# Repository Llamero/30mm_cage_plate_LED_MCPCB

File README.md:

# 30 mm Cage Plate LED Driver

## 4x LED 30 mm Cage Plate Board Description:
This board is an entirely self-contained LED and driver circuitry designed to be compatible with the Thorlabs 30 mm cage plate system: https://www.thorlabs.com/navigation.cfm?guide_id=2004  

The LEDs on the board are closely spaced so that all four LEDs efficiently couple into a 5 mm liquid light guide or other optical paths.

Each board can drive up to four individual LEDs, and includes a thermistor for temperature monitoring.  The the LED current is regulated by an [AL8843](https://www.diodes.com/part/view/AL8843), allowing LEDs to be driven with up to three amps of current.  The [AL8843](https://www.diodes.com/part/view/AL8843) also allows for both PWM control as well as analog current control down to 10% of the current limit (see below for setting max current limit).

Four p-channel mosfets on the board create a 1x4 multiplexer that allows individual LEDs to be toggled on by pulling the corresponding LED channel's gate to ground.  Each gate has a 4.7 kOhm pullup resistor so that each channel defaults to being off if not connected.

To turn the LEDs off more rapidly, there is also a 38V TVS diode parallel to the inductor that can be used to dump the residual energy stored in the inductor by setting all four multiplexer channels high.

A heatsink and fan can also be mounted to the backside of the cage plate for active cooling of high-current LEDs.

## 3x 30 mm Cage Plate Controller Description:
This repository also includes the design files for a controller that can operate up to three 30 mm cage plates for a total of 12 LEDs.

The controller is powered by a Teensy 4.1 which allows for precise timing control (<10 ns hysteresis) of each LED, as well a complex programmable control.  

On the back of the driver, each board connects to the driver via a shielded cat5 ethernet cable.  Additionally, there is a cat5 port with both a 12V supply and three channels of 5V PWM outputs for both powering the fans for each board as well as controlling the fan speed.  Finally, there are four protected digital inputs allowing for control signals up to -15V/+18V.

On the front of the driver, there is a potentiometer for controlling the intensity of each of the three LED boards, as well as a pushbutton to select the channel for each board.  Additionally, each pushbutton includes a red-green LED indicator to indicate which of the four LED channels is active.

## Driver Software:
There is software prewritten for the Teensy 4.1 that allows for both manual and programmable control, for syncing to triggers or other inputs.

Additionally, there is a GUI that allows for software control of the LED driver, we well as access to five preset programmable sync modes (digital, analog, confocal, serial, and custom), as well as custom configuration of the LED driver.

## Design:
To view and modify the board, download KiCAD https://www.kicad.org/, and open the project file.

Make sure to modify the LED footprint to match the footprint for your desired LEDs, and to change the current limit resistor to the desired value (see [AL8843](https://www.diodes.com/part/view/AL8843) datasheet, p. 11):
```
RSET (Ω)  Nominal Average Output Current (mA)
0.033     3,000
0.05      2,000
0.067     1,500
0.1       1,000
0.15      667
0.3       333
```
When changing the LED footprints, ensure that the LEDs remain closely spaced for efficient coupling into a liquid light guide.

## Ordering:
The BOM can be found here: 

This BOM includes all the parts needed to build both the LED driver boards as well as the LED controller board.

To order the PCBs, upload the Gerber files to your desired PCB vendor, such as: [https://www.pcbway.com/project/shareproject/W55957ASK98_30_mm_Cage_Plate_LED_MCPCB_kicad_pcb_3d2c1975.html](https://www.pcbway.com/project/shareproject/W55957ASK98_30_mm_Cage_Plate_LED_MCPCB_kicad_pcb_3d2c1975.html)  Make sure that the LED boards are MCPCBs and not FR4.  The driver board can be ordered as an FR4 board.

## Assembly:
To start, spread [thermal epoxy](https://www.digikey.com/en/products/detail/mg-chemicals/8329TCM-6ML/6035511) onto the flat side of a [Thorlabs 30 mm blank cage plate](https://www.thorlabs.com/thorproduct.cfm?partnumber=CP31).

Press the MCPCB board firmly to the cage plate using a vise or heavy weights.

Use a pipette tip or other fine tipped tool to remove excess epoxy from the cage rod holes.

Slide the board across the cage plate as needed to align the cage rod holes and allow the epoxy to cure overnight.

Next, assemble the board similarly to other reflow soldering boards. See the following manual: https://github.com/Llamero/Light_Color_and_Intensity_Datalogger/blob/master/Data%20logger%20assembly%20manual.pdf

Finally, use thermal epoxy to connect the heatsink to the Thorlabs cage plate, press firmly, and bake at 50°C overnight to cure.

.jpg)

## Operation:
Connect a 5V to 20V power supply, with the positive terminal connected to the Vin pin and the negative terminal connected to the Gnd pin. To control the LED current, you can send a +0.4V (10% current) to +2.5V (100% current) to the Ctrl pin. The LED can also be dimmed with PWM with a voltage up to 5V.  To control the mux, pull the channel you want to turn on to ground (0V).  To monitor temperature, measure the resistance of the thermistor.

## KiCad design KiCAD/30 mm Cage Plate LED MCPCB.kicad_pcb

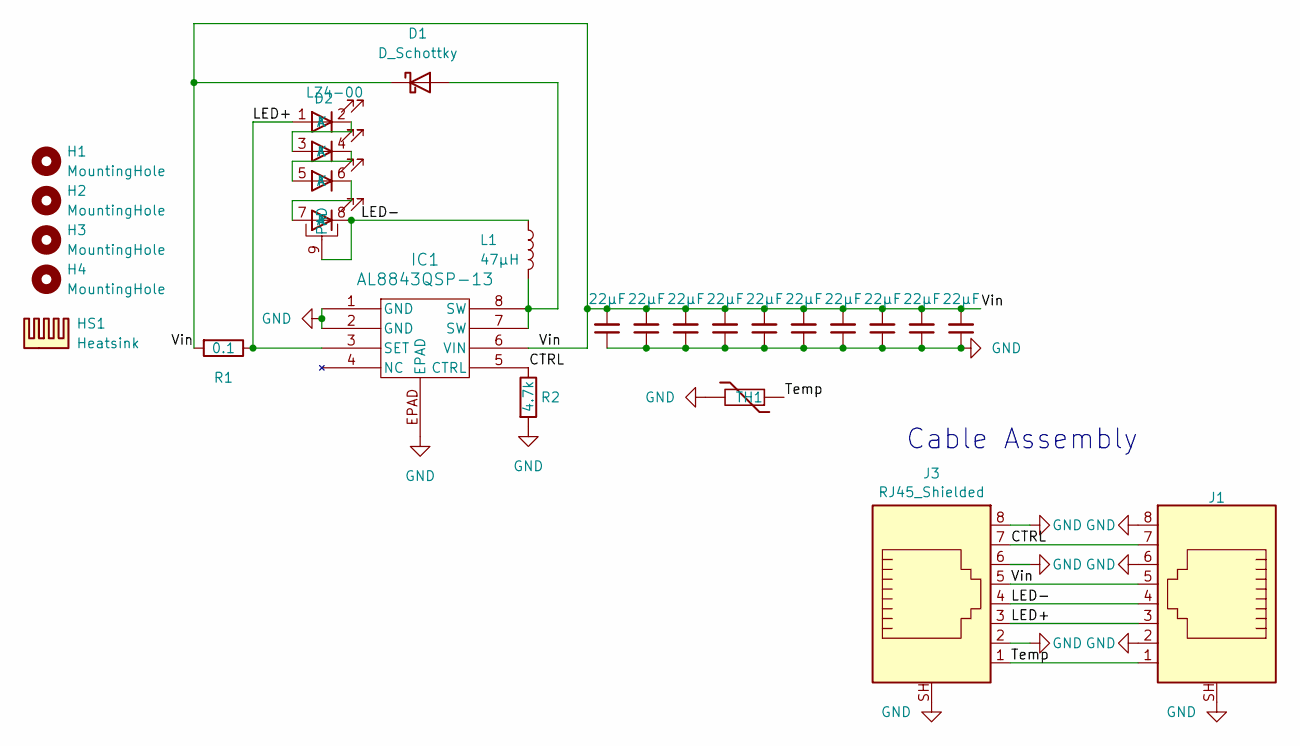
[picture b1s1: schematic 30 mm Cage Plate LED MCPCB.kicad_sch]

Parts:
C1, C2, C3, C4, C5, C6, C7, C8, C9, C10: 22µF; C_0805_2012Metric; Part CL21A226MAYNNNE
D1: D_Schottky; D_SOD-128; Part PMEG10030ELPX
D2: LZ4-00; Part LZ4-00R308-0000
H1, H2, H3, H4: MountingHole; 6MM NPTH
HS1: Heatsink; Part HSB38-707025P
IC1: AL8843QSP-13; SO-8EP_3P9X4P95_DIO; Part AL8843QSP-13
J1: 8P8C_Shielded; 1x RJ45; Part RJE3A1886102N
J3: RJ45_Shielded; Part AMJF0808-0100-GNB-26
L1: 47μH; SRP1038A-220M_BRN; Part SRP1038A-470M
R1: 0.1; R_1206_3216Metric; Part D1WRL1206L4R100D-T5
R2: 4.7k; C_0603_1608Metric; Part RG1608P-472-B-T5
TH1: Thermistor; R_0603_1608Metric; Part NCP18XM472J03RB

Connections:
/CTRL: IC1.5 (CTRL), J1.7, J3.7, R2.1
/LED+: D2.1 (A), IC1.3 (SET), J1.3, J3.3, R1.1
/LED-: D2.8 (K), D2.9 (PAD), J1.4, J3.4, L1.1
/Temp: J1.1, J3.1, TH1.1
/Vin: C1.2, C2.2, C3.2, C4.2, C5.2, C6.2, C7.2, C8.2, C9.2, C10.2, D1.1 (K), IC1.6 (VIN), J1.5, J3.5, R1.2
GND: C1.1, C2.1, C3.1, C4.1, C5.1, C6.1, C7.1, C8.1, C9.1, C10.1, IC1.1 (GND), IC1.2 (GND), IC1.EPAD, J1.2, J1.6, J1.8, J1.SH, J3.2, J3.6, J3.8, J3.SH, R2.2, TH1.2
unnamed: D1.2 (A), IC1.7 (SW), IC1.8 (SW), L1.2
unnamed: D2.2 (K), D2.3 (A)
unnamed: D2.4 (K), D2.5 (A)
unnamed: D2.6 (K), D2.7 (A)

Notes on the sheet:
Cable Assembly

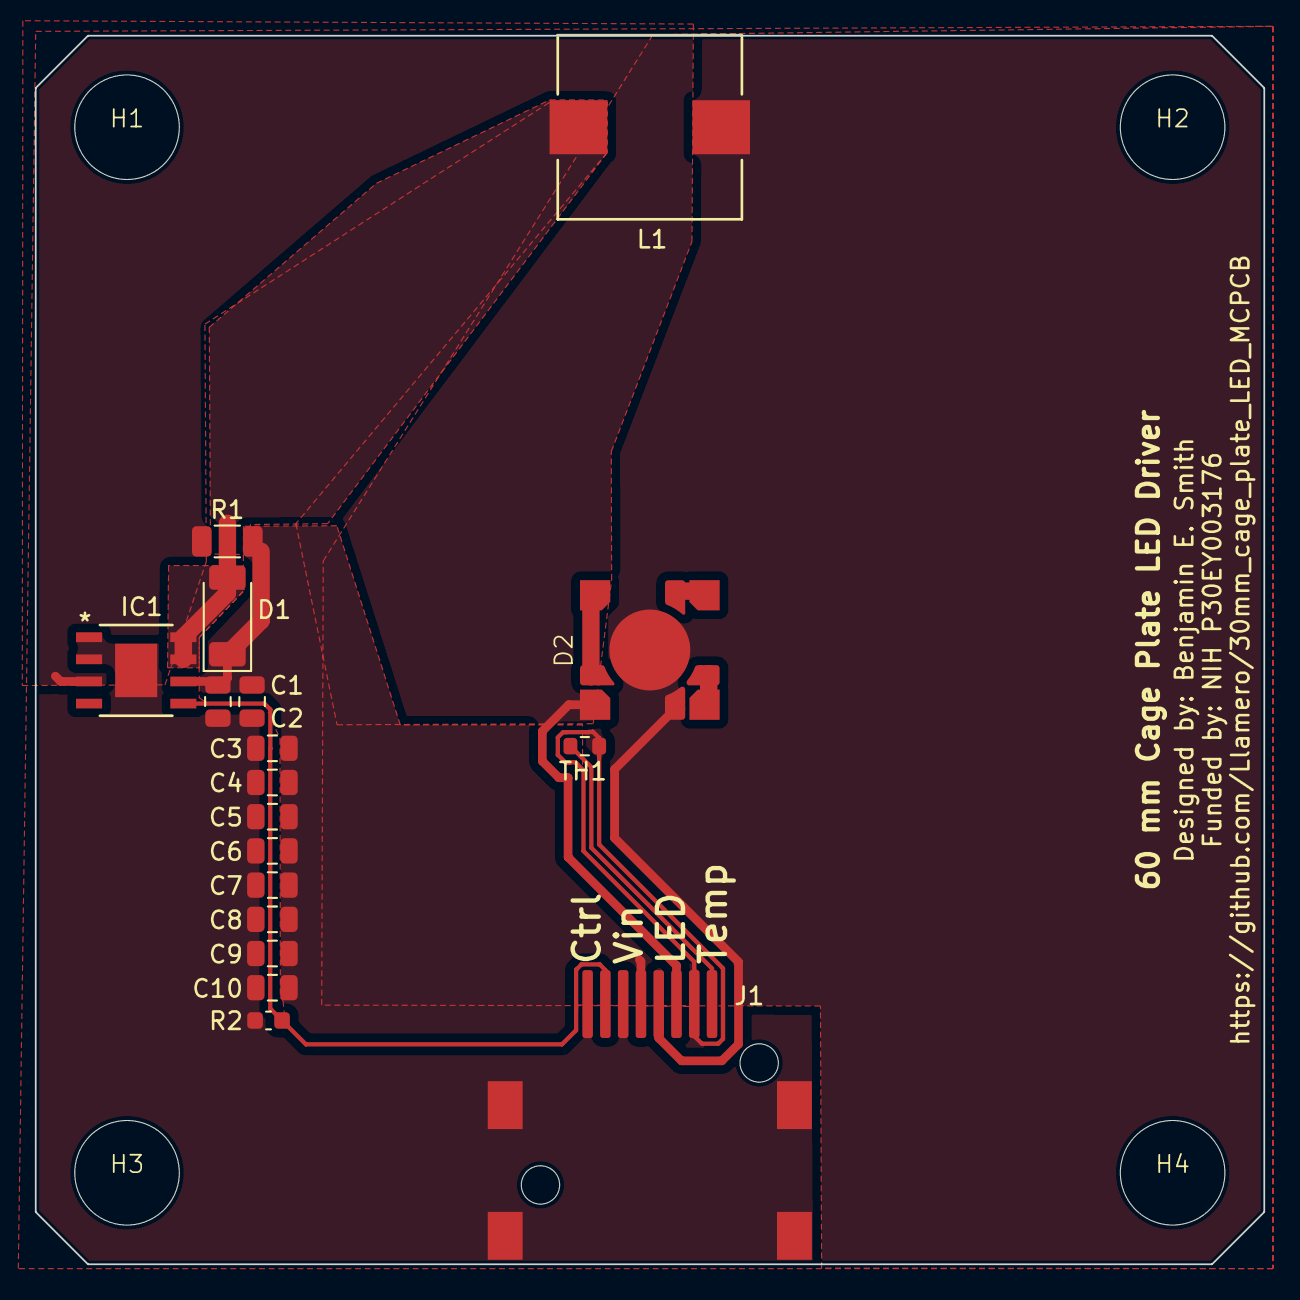
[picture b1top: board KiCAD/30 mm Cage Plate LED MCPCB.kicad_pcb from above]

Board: 2 copper layers, 70.5 x 70.5 mm, 22 parts (0 on the bottom side), 10 nets.

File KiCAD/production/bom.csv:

Designator,Footprint,Quantity,Value,LCSC Part #
"C1, C10, C2, C3, C4, C5, C6, C7, C8, C9",0805,10,22µF,
D1,D_SOD-128,1,D_Schottky,
D2,LZ4-00,1,LZ4-00,
"H1, H2, H3, H4",6MM NPTH,4,MountingHole,
IC1,SO-8EP_3P9X4P95_DIO,1,AL8843QSP-13,
J1,1x RJ45,1,8P8C_Shielded,
L1,SRP1038A-220M_BRN,1,47μH,
R1,1206,1,0.1,
R2,0603,1,4.7k,
TH1,0603,1,Thermistor,

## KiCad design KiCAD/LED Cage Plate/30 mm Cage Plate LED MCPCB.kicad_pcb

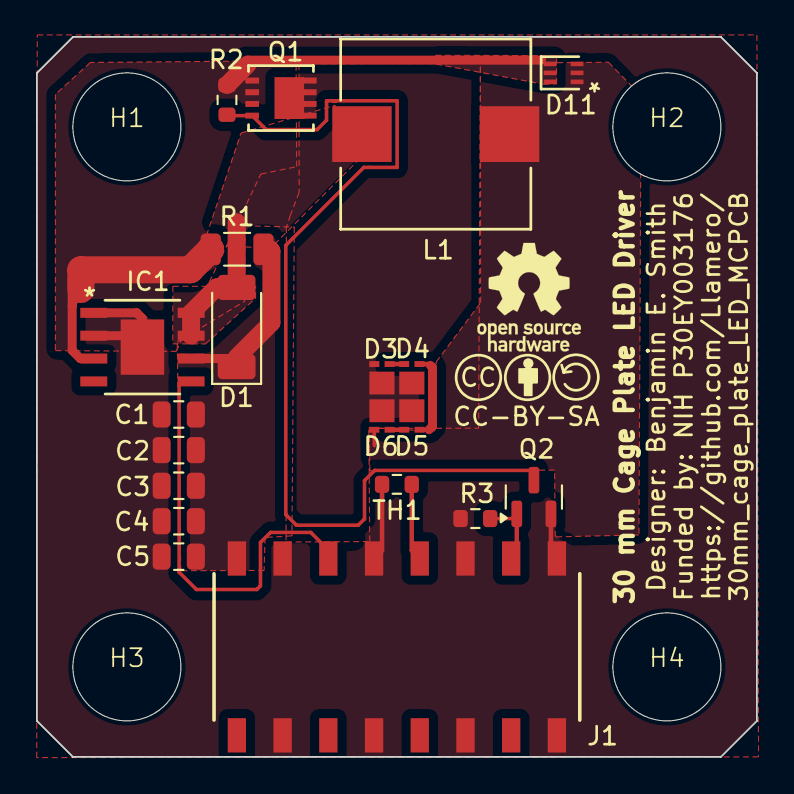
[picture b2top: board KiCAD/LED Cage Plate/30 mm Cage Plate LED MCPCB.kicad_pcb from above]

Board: 2 copper layers, 40.0 x 40.0 mm, 26 parts (0 on the bottom side), 13 nets.

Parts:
C1, C2, C3, C4, C5: 22μF; C_0805_2012Metric
D1: D_Schottky; D_SOD-128
D3, D4, D5, D6: LED_Pad; LED_XLAMP_XE-G_CRW
D11: D_Zener; DFN6_TDS3011_SEM
H1, H2, H3, H4: MountingHole; 6MM NPTH
IC1: AL8843QSP-13; SO-8EP_3P9X4P95_DIO
J1: Conn_01x08_Socket; SAMTEC_SSM-108-F-SH-TR
L1: 47μH; SRP1038A-220M_BRN
Q1: Q_PMOS; SON8_DMP4025SFGQ-13_DIO
Q2: Q_NMOS; SOT-23
R1: 0.040; R_1206_3216Metric
R2, R3: 10k; R_0603_1608Metric
SYM1: Logo_Open_Hardware_Small; OSHW-Logo_5.7x6mm_SilkScreen
SYM2: Logo_Open_Hardware_Small; CC-BY-SA Symbol
TH1: Thermistor; R_0603_1608Metric

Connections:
/Gate: J1.7, Q2.1 (G), R3.1
/LED+: D11.1 (K), IC1.3 (SET), Q1.1 (S), R1.1, R2.1
/LED-: D6.1 (K), D11.2 (A), L1.1
/PWM: IC1.5 (CTRL), J1.3
/Temp: J1.5, TH1.2
/Vin: C1.2, C2.2, C3.2, C4.2, C5.2, D1.1 (K), IC1.6 (VIN), J1.1, R1.2
GND: C1.1, C2.1, C3.1, C4.1, C5.1, IC1.1 (GND), IC1.2 (GND), IC1.EPAD, J1.2, J1.4, J1.6, J1.8, Q2.2 (S), R3.2, TH1.1
unnamed: D1.2 (A), IC1.7 (SW), IC1.8 (SW), L1.2
unnamed: D3.2 (A), D3.3 (PAD), D4.3 (PAD), D5.3 (PAD), D6.3 (PAD), Q1.3 (D)
unnamed: D3.1 (K), D4.2 (A)
unnamed: D4.1 (K), D5.2 (A)
unnamed: D5.1 (K), D6.2 (A)
unnamed: Q1.2 (G), Q2.3 (D), R2.2

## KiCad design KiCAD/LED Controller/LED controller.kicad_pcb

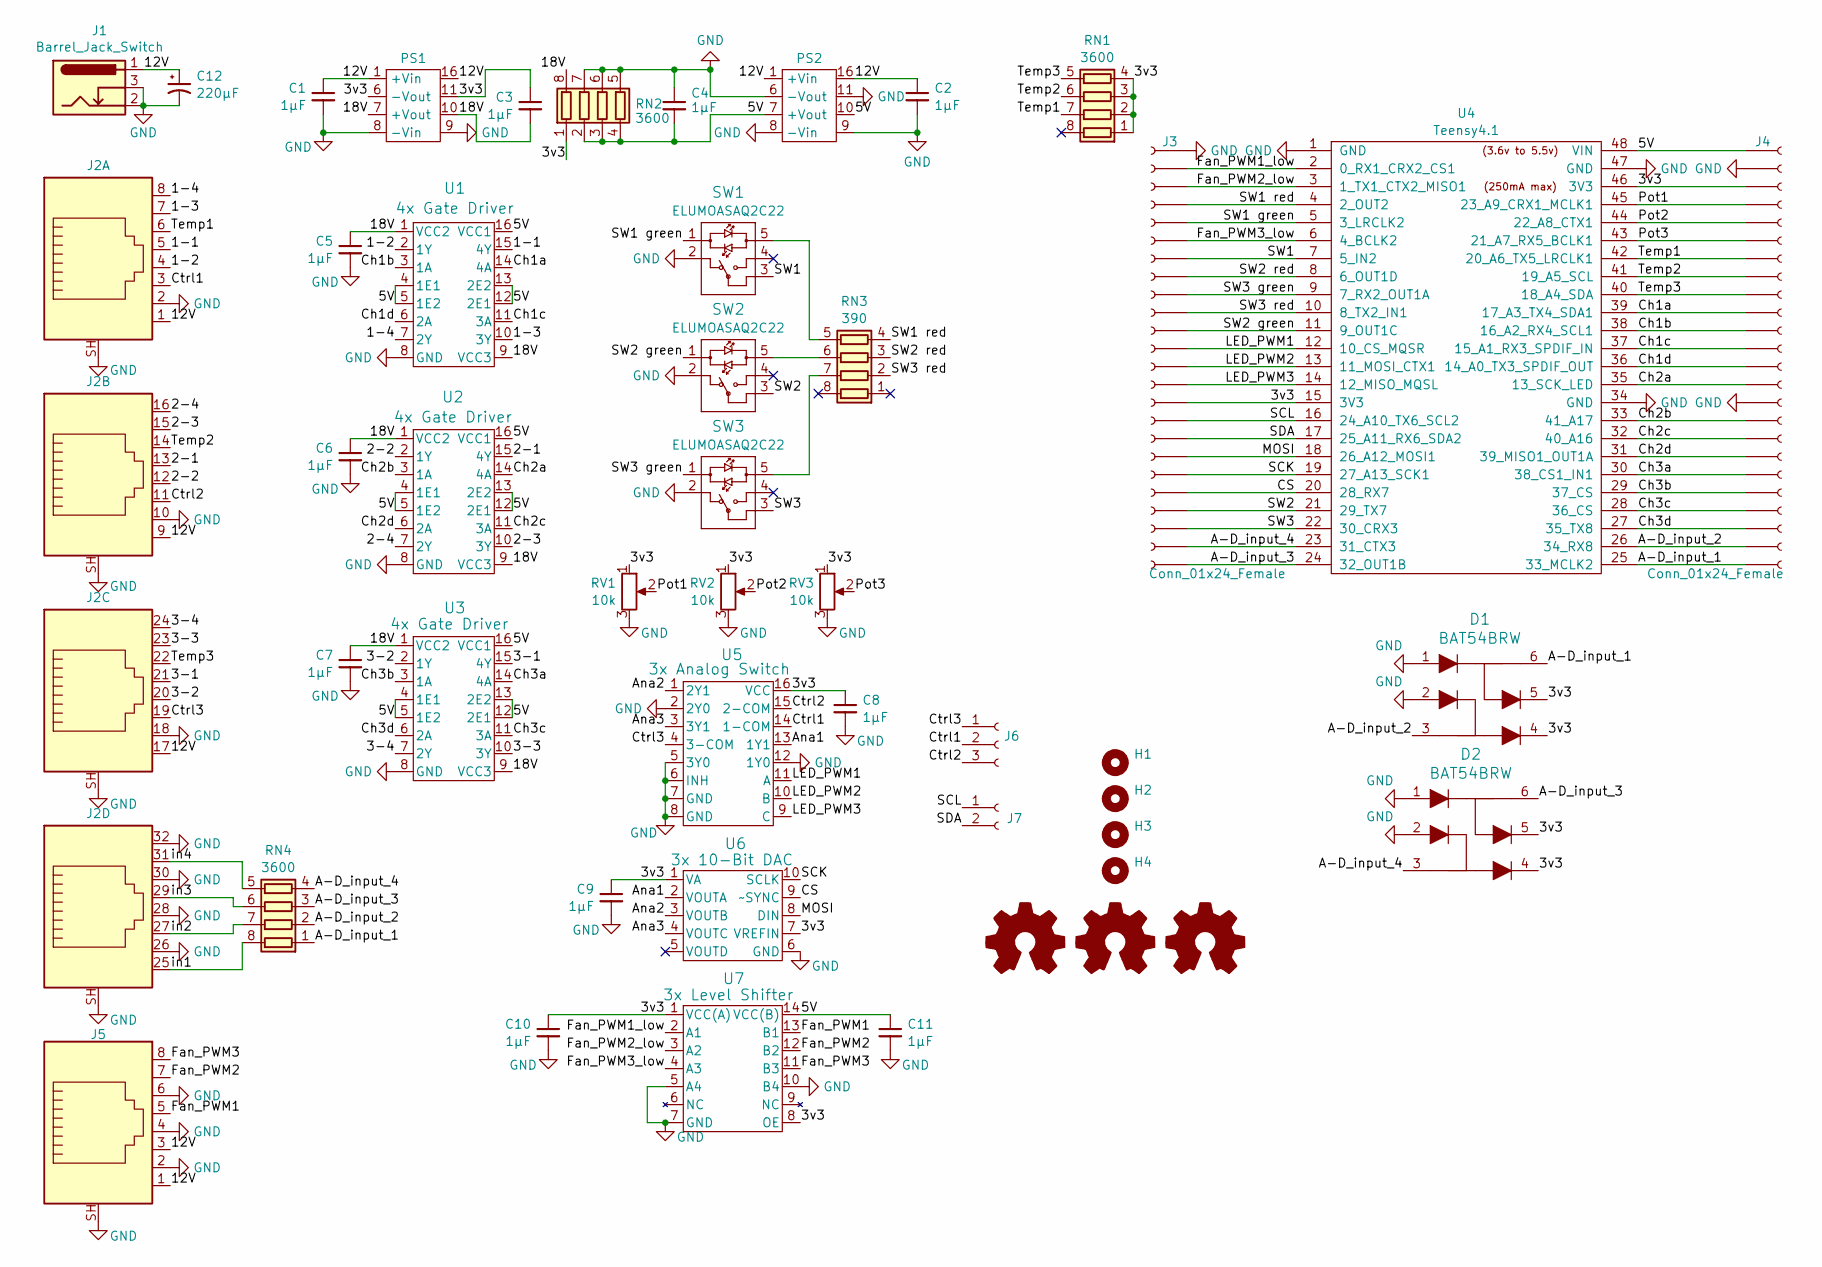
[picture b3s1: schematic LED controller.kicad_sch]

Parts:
C1, C2, C3, C4, C5, C6, C7, C8, C9, C10, C11: 1µF; C_0603_1608Metric; Part CL10A105KB8NNNC
C12: 220µF; CP_Radial_D6.3mm_P2.50mm; Part 25YXJ220M6.3X11
D1, D2: BAT54BRW; SOT-363_SC-70-6; Part BAT54BRW-7-F
H1, H2, H3, H4: MountingHole; 1-4_20 standoff; Part TN10-40-1/420-2
J1: Barrel_Jack_Switch; DC-jack_54-00165; Part # 54-00165
J2: 4x RJ45; RJ45_x4-RJSSE-5380-04; Part RJSSE-5380-04
J3, J4: Conn_01x24_Female; Part SSM-124-L-SV-LC
J5: 8P8C_Shielded; 1x RJ45; Part RJE3A1886102N
J6: Conn_01x03_Socket; PinSocket_1x03_P2.54mm_Vertical_SMD_Pin1Left; Part M20-7860346
J7: Conn_01x02_Socket; PinSocket_1x02_P2.54mm_Vertical; Part RS1-02-G
PS1: 15V DC-DC; SRS-1215-2; Part SRS-1215-2
PS2: 15V DC-DC; SRS-1215-2; Part SRS-1205-2
RN1, RN2, RN4: 3600; R_Array_Convex_4x0603; Part CAY16-362J4LF
RN3: 390; R_Array_Convex_4x0603; Part YC164-JR-07390RL
RV1, RV2, RV3: 10k; P160KN2-4QC20B10K; Part P160KN2-0QA25B10K
SW1, SW2, SW3: ELUMOASAQ2C22; ELUMOASAQ2C22_CNK; Part ELUMOASAQ2C22
SYM1: Logo_Open_Hardware_Small; CC-BY-SA Symbol
SYM2: Logo_Open_Hardware_Small; OSHW-Logo_5.7x6mm_SilkScreen
SYM3: Logo_Center_Positive; Polarity
U1, U2, U3: 4x Gate Driver; D16-4x gate driver; Part SN75374D
U4: Teensy4.1; Teensy_3_6_with_headers; Part 1568-DEV-16996-ND
U5: 3x Analog Switch; SN74LV4053ADR; Part SN74LV4053ADR
U6: 3x 10-Bit DAC; DAC084S085CIMMXNOPB; Part DAC104S085QIMMX/NOPB
U7: 3x Level Shifter; TSSOP14_NXB0104_NEX; Part NXB0104PWJ

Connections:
/1-1: J2.5, U1.15 (4Y)
/1-2: J2.4, U1.2 (1Y)
/1-3: J2.7, U1.10 (3Y)
/1-4: J2.8, U1.7 (2Y)
/2-1: J2.13, U2.15 (4Y)
/2-2: J2.12, U2.2 (1Y)
/2-3: J2.15, U2.10 (3Y)
/2-4: J2.16, U2.7 (2Y)
/3-1: J2.21, U3.15 (4Y)
/3-2: J2.20, U3.2 (1Y)
/3-3: J2.23, U3.10 (3Y)
/3-4: J2.24, U3.7 (2Y)
/3v3: C3.1, C8.1, C9.1, C10.1, D1.4, D1.5, D2.4, D2.5, J3.~, J4.~, PS1.6 (-Vout), PS1.11, RN1.1 (R1.1), RN1.2 (R2.1), RN1.3 (R3.1), RN1.4 (R4.1), RN2.1 (R1.1), RV1.1, RV2.1, RV3.1, U4.15 (3V3), U4.46 (3V3), U5.16 (VCC), U6.1 (VA), U6.7 (VREFIN), U7.1 (VCC(A)), U7.8 (OE)
/5V: C4.2, C11.1, J4.~, PS2.7 (+Vout), PS2.10, RN2.2 (R2.1), RN2.3 (R3.1), RN2.4 (R4.1), U1.4 (1E1), U1.5 (1E2), U1.12 (2E1), U1.13 (2E2), U1.16 (VCC1), U2.4 (1E1), U2.5 (1E2), U2.12 (2E1), U2.13 (2E2), U2.16 (VCC1), U3.4 (1E1), U3.5 (1E2), U3.12 (2E1), U3.13 (2E2), U3.16 (VCC1), U4.48 (VIN), U7.14 (VCC(B))
/12V: C1.1, C2.1, C12.1, J1.1, J2.1, J2.9, J2.17, J5.1, J5.3, PS1.1 (+Vin), PS1.16, PS2.1 (+Vin), PS2.16
/18V: C3.2, C5.1, C6.1, C7.1, PS1.7 (+Vout), PS1.10, RN2.8 (R1.2), U1.1 (VCC2), U1.9 (VCC3), U2.1 (VCC2), U2.9 (VCC3), U3.1 (VCC2), U3.9 (VCC3)
/A-D_input_1: D1.6, J4.~, RN4.1 (R1.1), U4.25 (33_MCLK2)
/A-D_input_2: D1.3, J4.~, RN4.2 (R2.1), U4.26 (34_RX8)
/A-D_input_3: D2.6, J3.~, RN4.3 (R3.1), U4.24 (32_OUT1B)
/A-D_input_4: D2.3, J3.~, RN4.4 (R4.1), U4.23 (31_CTX3)
/Ana1: U5.13 (1Y1), U6.2 (VOUTA)
/Ana2: U5.1 (2Y1), U6.3 (VOUTB)
/Ana3: U5.3 (3Y1), U6.4 (VOUTC)
/CS: J3.~, U4.20 (28_RX7), U6.9 (~SYNC)
/Ch1a: J4.~, U1.14 (4A), U4.39 (17_A3_TX4_SDA1)
/Ch1b: J4.~, U1.3 (1A), U4.38 (16_A2_RX4_SCL1)
/Ch1c: J4.~, U1.11 (3A), U4.37 (15_A1_RX3_SPDIF_IN)
/Ch1d: J4.~, U1.6 (2A), U4.36 (14_A0_TX3_SPDIF_OUT)
/Ch2a: J4.~, U2.14 (4A), U4.35 (13_SCK_LED)
/Ch2b: J4.~, U2.3 (1A), U4.33 (41_A17)
/Ch2c: J4.~, U2.11 (3A), U4.32 (40_A16)
/Ch2d: J4.~, U2.6 (2A), U4.31 (39_MISO1_OUT1A)
/Ch3a: J4.~, U3.14 (4A), U4.30 (38_CS1_IN1)
/Ch3b: J4.~, U3.3 (1A), U4.29 (37_CS)
/Ch3c: J4.~, U3.11 (3A), U4.28 (36_CS)
/Ch3d: J4.~, U3.6 (2A), U4.27 (35_TX8)
/Ctrl1: J2.3, J6.2, U5.14 (1-COM)
/Ctrl2: J2.11, J6.3, U5.15 (2-COM)
/Ctrl3: J2.19, J6.1, U5.4 (3-COM)
/Fan_PWM1: J5.5, U7.13 (B1)
/Fan_PWM1_low: J3.~, U4.2 (0_RX1_CRX2_CS1), U7.2 (A1)
/Fan_PWM2: J5.7, U7.12 (B2)
/Fan_PWM2_low: J3.~, U4.3 (1_TX1_CTX2_MISO1), U7.3 (A2)
/Fan_PWM3: J5.8, U7.11 (B3)
/Fan_PWM3_low: J3.~, U4.6 (4_BCLK2), U7.4 (A3)
/LED_PWM1: J3.~, U4.12 (10_CS_MQSR), U5.11 (A)
/LED_PWM2: J3.~, U4.13 (11_MOSI_CTX1), U5.10 (B)
/LED_PWM3: J3.~, U4.14 (12_MISO_MQSL), U5.9 (C)
/MOSI: J3.~, U4.18 (26_A12_MOSI1), U6.8 (DIN)
/Pot1: J4.~, RV1.2, U4.45 (23_A9_CRX1_MCLK1)
/Pot2: J4.~, RV2.2, U4.44 (22_A8_CTX1)
/Pot3: J4.~, RV3.2, U4.43 (21_A7_RX5_BCLK1)
/SCK: J3.~, U4.19 (27_A13_SCK1), U6.10 (SCLK)
/SCL: J3.~, J7.1, U4.16 (24_A10_TX6_SCL2)
/SDA: J3.~, J7.2, U4.17 (25_A11_RX6_SDA2)
/SW1: J3.~, SW1.3, U4.7 (5_IN2)
/SW1 green: J3.~, SW1.1, U4.5 (3_LRCLK2)
/SW1 red: J3.~, RN3.4 (R4.1), U4.4 (2_OUT2)
/SW2: J3.~, SW2.3, U4.21 (29_TX7)
/SW2 green: J3.~, SW2.1, U4.11 (9_OUT1C)
/SW2 red: J3.~, RN3.3 (R3.1), U4.8 (6_OUT1D)
/SW3: J3.~, SW3.3, U4.22 (30_CRX3)
/SW3 green: J3.~, SW3.1, U4.9 (7_RX2_OUT1A)
/SW3 red: J3.~, RN3.2 (R2.1), U4.10 (8_TX2_IN1)
/Temp1: J2.6, J4.~, RN1.7 (R2.2), U4.42 (20_A6_TX5_LRCLK1)
/Temp2: J2.14, J4.~, RN1.6 (R3.2), U4.41 (19_A5_SCL)
/Temp3: J2.22, J4.~, RN1.5 (R4.2), U4.40 (18_A4_SDA)
/in1: J2.25, RN4.8 (R1.2)
/in2: J2.27, RN4.7 (R2.2)
/in3: J2.29, RN4.6 (R3.2)
/in4: J2.31, RN4.5 (R4.2)
GND: C1.2, C2.2, C4.1, C5.2, C6.2, C7.2, C8.2, C9.2, C10.2, C11.2, C12.2, D1.1, D1.2, D2.1, D2.2, J1.2, J1.3, J2.2, J2.10, J2.18, J2.26, J2.28, J2.30, J2.32, J2.SH, J3.~, J4.~, J5.2, J5.4, J5.6, J5.SH, PS1.8 (-Vin), PS1.9, PS2.6 (-Vout), PS2.8 (-Vin), PS2.9, PS2.11, RN2.5 (R4.2), RN2.6 (R3.2), RN2.7 (R2.2), RV1.3, RV2.3, RV3.3, SW1.2, SW2.2, SW3.2, U1.8 (GND), U2.8 (GND), U3.8 (GND), U4.1 (GND), U4.34 (GND), U4.47 (GND), U5.2 (2Y0), U5.5 (3Y0), U5.6 (INH), U5.7 (GND), U5.8 (GND), U5.12 (1Y0), U6.6 (GND), U7.5 (A4), U7.7 (GND), U7.10 (B4)
unnamed: RN3.7 (R2.2), SW3.5
unnamed: RN3.6 (R3.2), SW2.5
unnamed: RN3.5 (R4.2), SW1.5

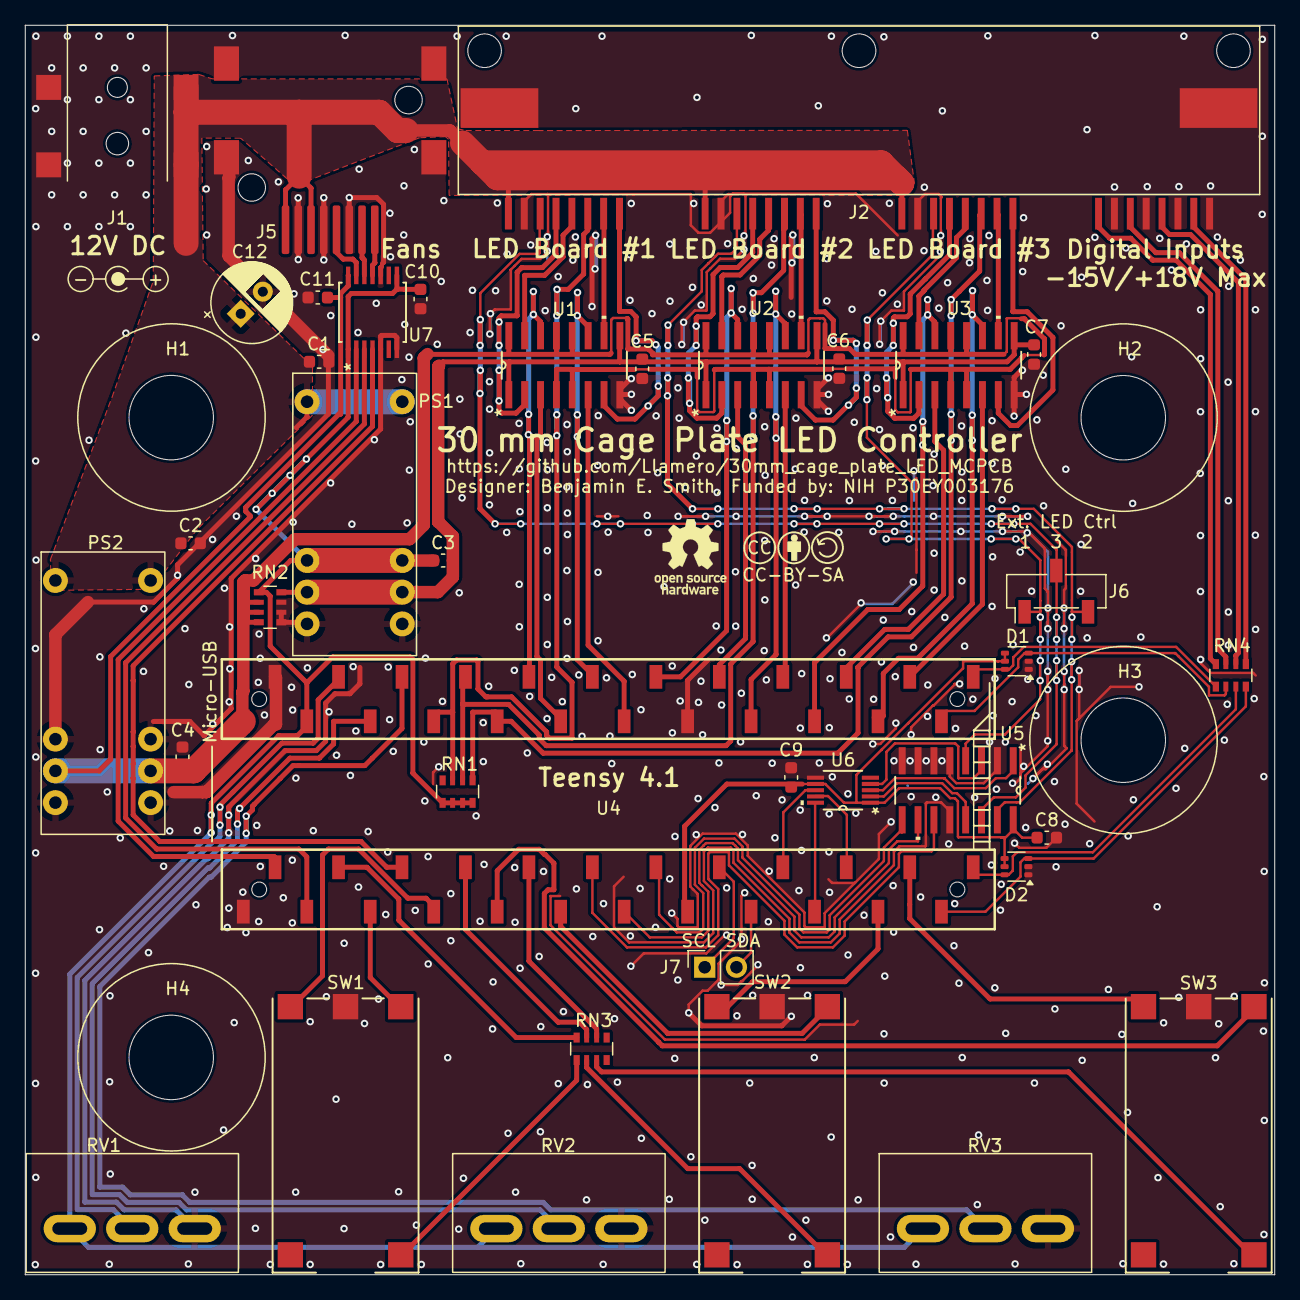
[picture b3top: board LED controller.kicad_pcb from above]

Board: 2 copper layers, 100.0 x 100.0 mm, 45 parts (0 on the bottom side), 75 nets.

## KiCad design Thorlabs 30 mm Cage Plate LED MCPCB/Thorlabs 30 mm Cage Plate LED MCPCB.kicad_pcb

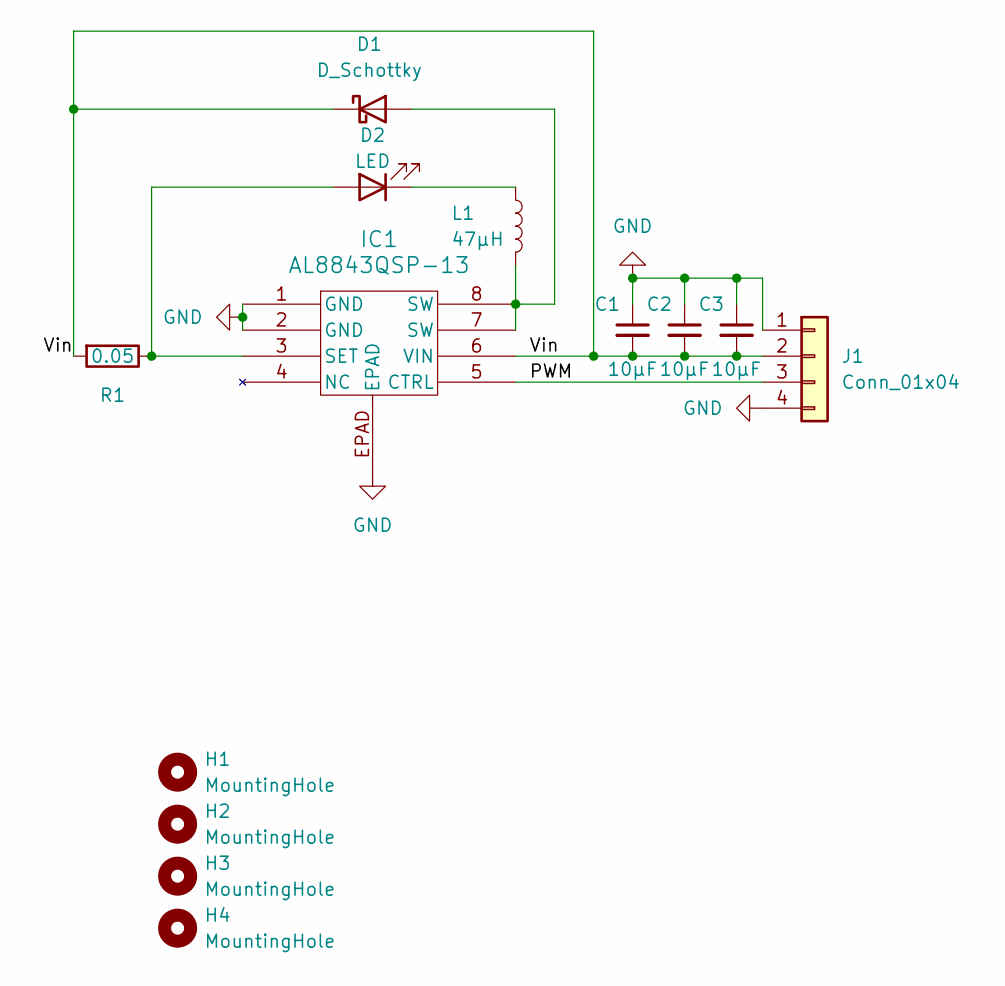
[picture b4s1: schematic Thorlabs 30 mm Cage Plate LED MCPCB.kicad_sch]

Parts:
C1, C2, C3: 10μF; C_0603_1608Metric; Part GRM188R6YA106MA73D
D1: D_Schottky; D_SOD-128; Part PMEG10030ELPX
D2: LED; LED_SST-20-DR; Part SST-20-DR-B120H-AA660
H1, H2, H3, H4: MountingHole; 6MM NPTH
IC1: AL8843QSP-13; SO-8EP_3P9X4P95_DIO; Part AL8843QSP-13
J1: Conn_01x04; SAMTEC_SSM-104-L-SH; Part SSM-104-F-SH-TR
L1: 47μH; SRP1038A-220M_BRN; Part SRP1038A-470M
R1: 0.05; R_1206_3216Metric; Part MCS1632R050FER

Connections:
/PWM: IC1.5 (CTRL), J1.3
/Vin: C1.2, C2.2, C3.2, D1.1 (K), IC1.6 (VIN), J1.2, R1.2
GND: C1.1, C2.1, C3.1, IC1.1 (GND), IC1.2 (GND), IC1.EPAD, J1.1, J1.4
unnamed: D1.2 (A), IC1.7 (SW), IC1.8 (SW), L1.2
unnamed: D2.2 (A), IC1.3 (SET), R1.1
unnamed: D2.1 (K), L1.1

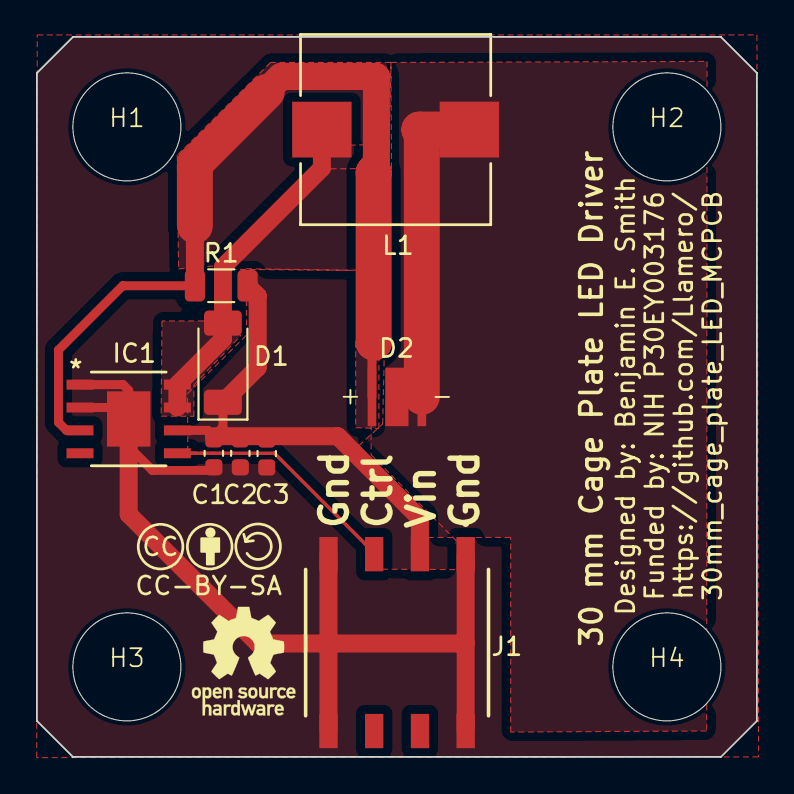
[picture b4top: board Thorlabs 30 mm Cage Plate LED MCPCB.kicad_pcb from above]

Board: 2 copper layers, 40.0 x 40.0 mm, 13 parts (0 on the bottom side), 6 nets.

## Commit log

2023-11-01 Add core components to schematic
2023-11-02 Rats nest connected
2023-11-03 Full working draft
2023-11-03 PCB optimization
2023-11-03 Gerber files added
2023-11-03 Add CAD model of setup
2023-11-29 Add heatsink
2023-11-29 Update naming
2023-12-20 Add images
2023-12-21 Update README.md
    Add order info
2023-12-21 Update README.md
    Add assembly info
2024-01-12 Move PWM and Vin pins apart to prevent fatal shorts of Vin to Ctrl
2024-11-08 working draft
2024-11-09 Before adding mux to PCB
2024-11-09 Fan added
2024-11-09 Add logo
2024-11-09 Update LICENSE
    Add CC license for PCB
2024-11-09 Add OSHW logo
2024-11-09 More copper for LEDs, OSHW logo
2024-11-14 Add pmos array mux
2024-11-15 pmos mux connected - better conduction path
2024-11-16 Start on driver board
2024-11-21 Working draft of driver circuit
2024-11-21 bypass caps added
2024-11-22 Partial PCB layout
2024-11-23 Input jack added
2024-11-23 Add I/O jack, and re-route
2024-11-23 more traces added - better grounding
2024-11-25 All but caps connected
2024-11-26 All connected - pass DRC
2024-11-26 Better 18V cap placement
2024-11-26 Labels added
2024-11-26 I2C and external LED connector added - Pass DRC
2024-11-26 Minor changes - ground strip along RJ45 12V, add part # for I2C socket
2024-11-26 Label schematic - switch to 10-bit DAC
2024-11-27 Improve clearance of gate traces on LED plate
2024-12-03 Ordered version
2024-12-22 CAD model for LED setup
2025-01-16 Change level shifter IC
2025-01-17 Start porting 4x LED code over - Pin.h done
2025-01-17 Fix default therm series resistor
2025-01-17 Initial draft of structs and unions compiles
2025-01-18 Button to select channels and knob for intensity implemented
2025-01-18 Increase ADC precision
2025-01-21 Untested initial DAC class
2025-01-22 Initial DAC working tests
2025-01-23 Add notes for revision to controller board
2025-01-24 Draft of initialize works
2025-01-24 Update intensity and initialize works
2025-01-25 manual controls working
2025-01-29 Faster update intensity, stable fans,
2025-01-29 Serial compiles, untested
2025-01-29 Fix disconnect thermal fault
2025-01-29 Set channels to be 0->N_LEDS -1
2025-01-30 Preliminary revisions to GUI mapper
2025-01-31 Update main window widgets
2025-02-01 New GUI boots!
2025-02-01 Lamda calls can now be looped!
    Using sender() to get the objectName of the sending widget fixes issues with loops and lamda functions
2025-02-05 start fixing sync config
2025-02-06 Start updating status
2025-02-11 update status
2025-02-12 Partial SD fix - format works
2025-02-13 Board boots without errors
2025-02-16 More status updates
2025-02-17 Status window fully working
2025-02-17 Update default GUI state
2025-02-18 Manual GUI works completely
2025-02-18 Add single period settling delay on led PWM
    PWM bus appears to need one full period to settle before applying current, otherwise the LED with flash when changing from constant current to PWM.
2025-02-18 Fix status plots and temp min max
2025-02-18 Check board disables all 4 LEDs in config
2025-02-18 Driver control mode fully working
2025-02-19 Fix switching between manual and GUI control
2025-02-19 Start integrating digital sync
2025-02-20 Fix sync packing, sequence, status window, serial disconnect
    Digital sync is working, sequence tables can now be uploaded, USB disconnects are handled cleanly.
2025-02-20 Remove LED offset in initialize Seq since GUI now does offset
2025-02-20 Add update flag to manual setting of sync mode
2025-03-25 Fix custom sync and sync gui
2025-03-26 Fix status plots and current limits in GUI
2025-04-10 Update README.md
    Change order of assebly steps
2025-04-22 Only pulse the mosfet open for proper current behavior
2025-04-22 Only pulse once at LED off.
2025-07-16 add BOM
2025-07-16 Update pins
2025-07-16 Add more images
2025-07-16 fix image
2025-07-16 rotate image
2025-07-16 Add assembly images
2025-07-17 add soldering images
2025-07-17 Clean up Teensy code repository
2025-07-17 Update BOM
2025-07-23 Fix Tetrascope display sync
2025-07-26 Working draft of series LED - passes DRC
2025-07-29 Remove ! from links
2025-07-29 Fix BOM link
2025-07-29 Update BOM to red LED
2025-07-30 minor optimizations
2025-08-01 update pins to revised version
2025-11-13 Imrpoved design - more caps and therm
2025-11-14 60 mm plate with flat 8x connector
2025-11-14 CAD mockup
2025-11-19 Add T-cube connectivity
